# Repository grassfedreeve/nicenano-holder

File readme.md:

## Holder PCB for nice!nano

### nice!nano v2 holder PCB for Bastard Keyboards Charybdis
### WARNING: The PCBs have been printed and tested, however not an Electrical Engineer use at your own risk and go over the files before ordering any prototypes.

### Features:
- matrix pinout moved to low frequency pins
- spi trackball connection moved to high frequency pins
- removed rgb and serial connection
- repositioned reset footprint
- replaced and repositioned on/off
- ph2 battery connector

## BOM

Power Switch: https://au.mouser.com/ProductDetail/CK/JS202011CQN?qs=LgMIjt8LuD%2Fe%2BE3iTcEFYw%3D%3D&countryCode=AU&currencyCode=AUD

Reset Button: Button, 4x4x1.5 https://www.aliexpress.com/item/1005001304569553.html?spm=a2g0s.9042311.0.0.27424c4dDwgcp7

Ultra Low Profile Sockets: 315-43-164-41-003000
Other sockets will not be low enough to fit USBC cutout.

# License 

This work is licensed under a Creative Commons Attribution-NonCommercial-ShareAlike 4.0 International License.

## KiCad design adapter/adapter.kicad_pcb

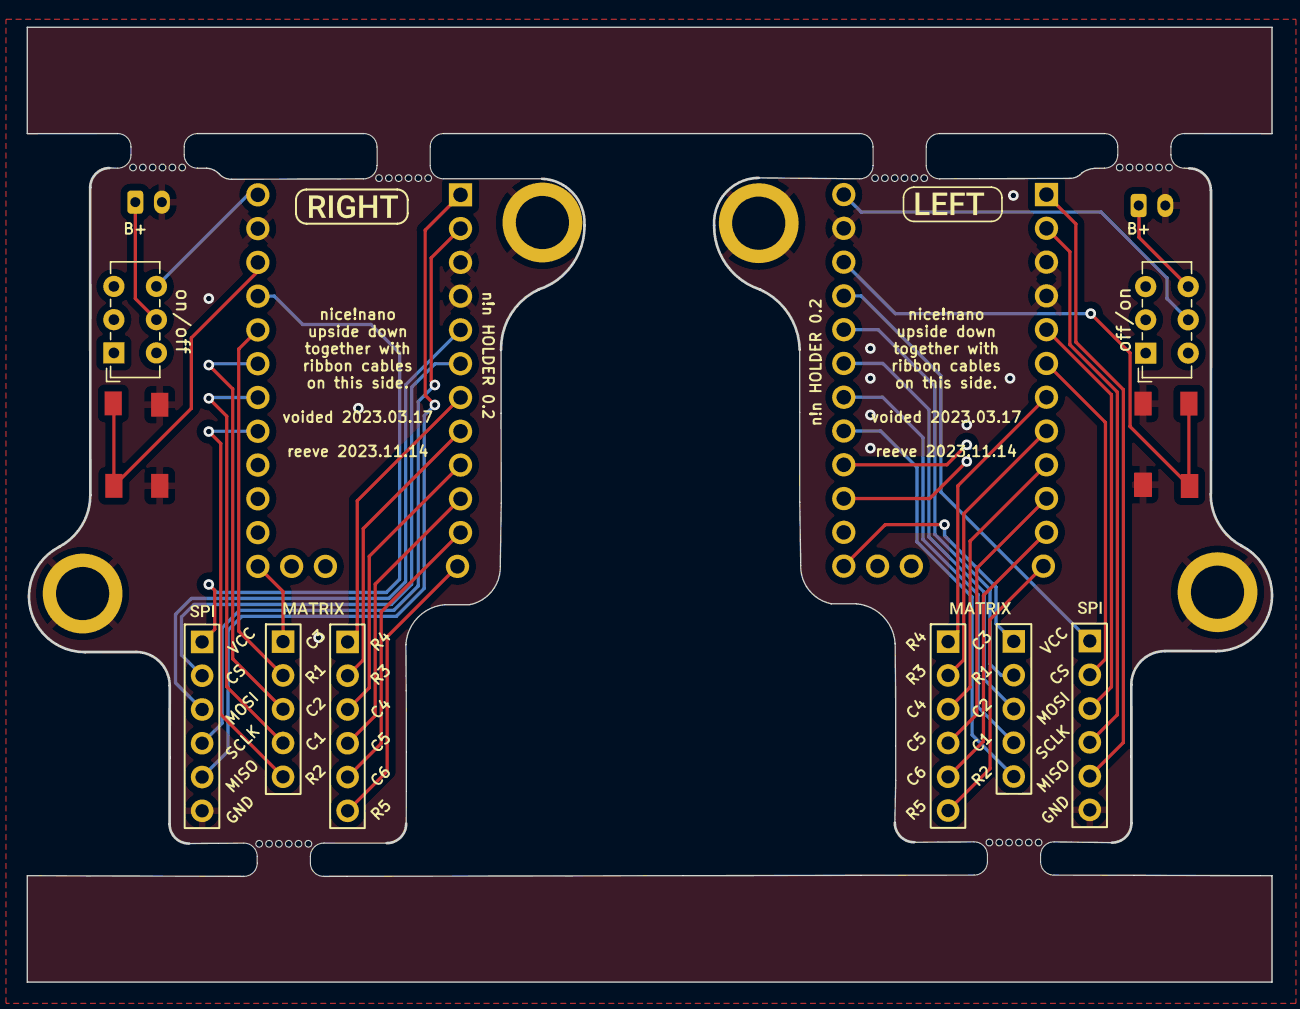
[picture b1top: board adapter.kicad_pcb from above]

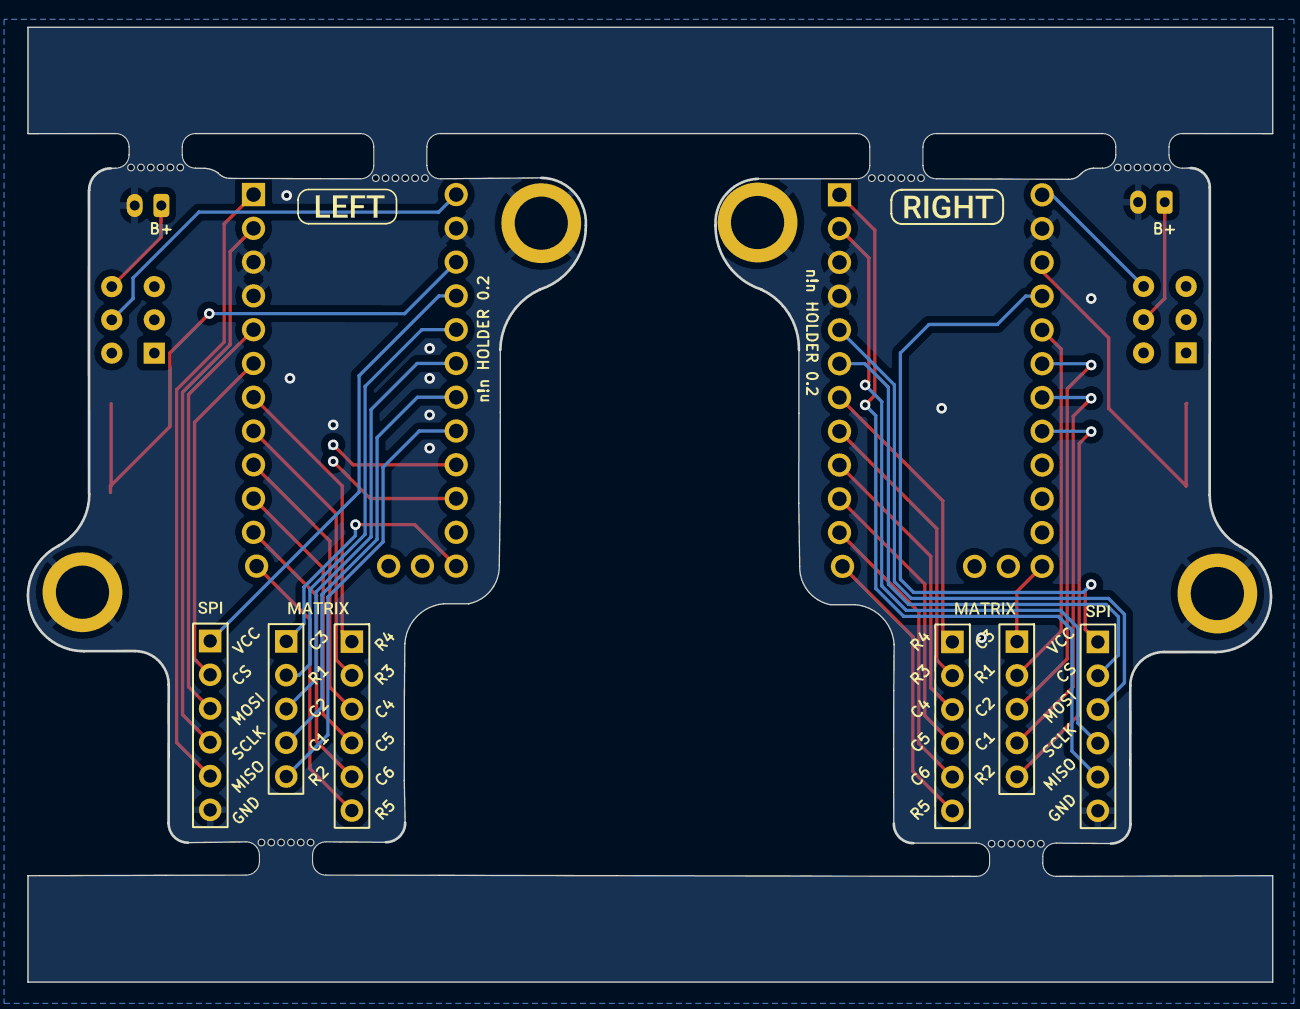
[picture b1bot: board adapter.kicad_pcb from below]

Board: 2 copper layers, 93.6 x 71.8 mm, 29 parts (8 on the bottom side), 36 nets.

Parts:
H1, H2, H3, H4: M4; MountingHole_4mm_Pad_thin
J3, J6: battery charge; JST_PH_B2B-PH-K_1x02_P2.00mm_Vertical
J7, J8: trackball; 6_PinHeader
J9, J11: Ribbon; 5_PinHeader
J10, J12: Ribbon; 6_PinHeader
SW1, SW2: SW_SPST; PushSwitch
U1, U2: eliteC; Elite-C
kibuzzard-61F01B61, kibuzzard-61F01B61#2: G***; kibuzzard-61F01B61
kibuzzard-61F01940, kibuzzard-61F01940#2, kibuzzard-61F01940#3, kibuzzard-61F01940#4: G***; kibuzzard-61F01940
kibuzzard-61F01957, kibuzzard-61F01957#2, kibuzzard-61F01957#3, kibuzzard-61F01957#4: G***; kibuzzard-61F01957
kibuzzard-6208EFFE, kibuzzard-6208EFFE#2: G***; kibuzzard-6208EFFE
off/on: SW_E-Switch_EG1271_SPDT

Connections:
+5V: J7.1, J8.1, U1.21 (VCC), U2.21 (VCC)
GND: H1.1, H2.1, H3.1, H4.1, J3.2, J6.2, J7.6, J8.6, SW1.2 (B), SW2.2 (B), U1.3 (GND), U1.4 (GND), U1.23 (GND), U2.3 (GND), U2.4 (GND), U2.23 (GND)
Rst: SW1.1 (A), U1.22 (RST)
Rst2: SW2.1 (A), U2.22 (RST)
bat_r: U2.24 (RAW), off/on.5
bat_sw_r: J6.1, off/on.6
col1_l: J9.4, U1.18 (F6)
col1_r: J11.4, U2.18 (F6)
col2_l: J9.3, U1.19 (F5)
col2_r: J11.3, U2.19 (F5)
col3_l: J9.1, U1.13 (B6)
col3_r: J11.1, U2.13 (B6)
col4_l: J10.3, U1.9 (D7)
col4_r: J12.3, U2.9 (D7)
col5_l: J10.4, U1.10 (E6)
col5_r: J12.4, U2.10 (E6)
col6_l: J10.5, U1.11 (B4)
col6_r: J12.5, U2.11 (B4)
miso_l: J7.5, U1.1 (TX)
miso_r: J8.5, U2.1 (TX)
mosi_l: J7.3, U1.5 (SCL)
mosi_r: J8.3, U2.5 (SCL)
row1_l: J9.2, U1.20 (F4)
row1_r: J11.2, U2.20 (F4)
row2_l: J9.5, U1.17 (F7)
row2_r: J11.5, U2.17 (F7)
row3_l: J10.2, U1.8 (C6)
row3_r: J12.2, U2.8 (C6)
row4_l: J10.1, U1.7 (D4)
row4_r: J12.1, U2.7 (D4)
row5_l: J10.6, U1.12 (B5)
row5_r: J12.6, U2.12 (B5)
sc_l: J7.4, U1.2 (RX)
sc_r: J8.4, U2.2 (RX)
ss_l: J7.2, U1.6 (SDA)
ss_r: J8.2, U2.6 (SDA)

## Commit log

2023-11-17 gerber
2023-11-17 v0.2
    removed serial ports
    moved reset to be reachable
    replace on/off switch to top and swapped to vertical through hole
2023-11-26 Small fixes
2023-11-26 Updated Gerber
